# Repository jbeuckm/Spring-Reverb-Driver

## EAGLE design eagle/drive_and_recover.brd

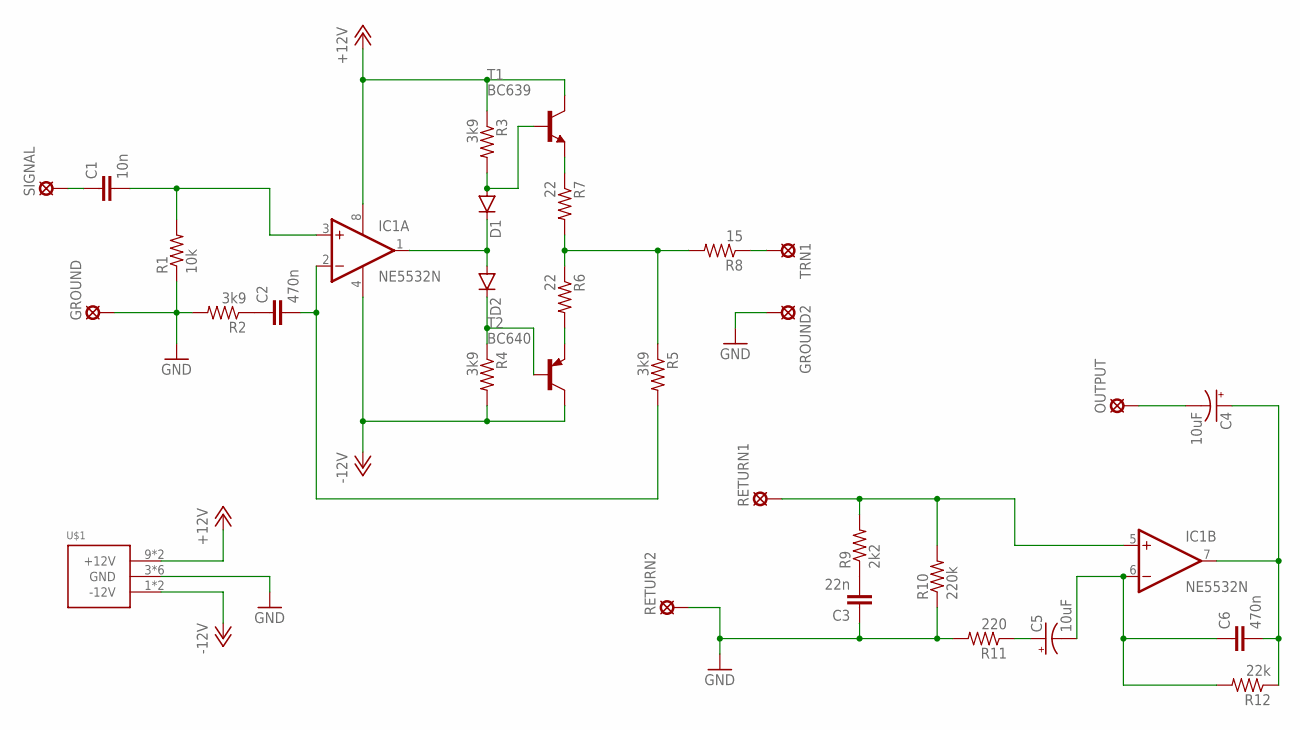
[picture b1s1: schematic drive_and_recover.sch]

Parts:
C1: 10n; CAP-PTH-SMALL
C2, C6: 470n; CAP-PTH-SMALL
C3: 22n; CAP-PTH-SMALL
C4, C5: 10uF; E2-5
D1, D2: DIODE1N4148; DIODE-1N4148
GROUND, GROUND2: LSP10
IC1: NE5532N; DIL08
OUTPUT: LSP10
R1: 10k; AXIAL-0.4
R2, R3, R4, R5: 3k9; AXIAL-0.4
R6, R7: 22; AXIAL-0.4
R8: 15; AXIAL-0.4
R9: 2k2; AXIAL-0.4
R10: 220k; AXIAL-0.4
R11: 220; AXIAL-0.4
R12: 22k; AXIAL-0.4
RETURN1, RETURN2: LSP10
SIGNAL: LSP10
T1: BC639; TO92-ECB
T2: BC640; TO92-BCE
TRN1: LSP10
U$1: POWER_SIMPLE16; POWER_16

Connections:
+12V: IC1.8 (V+), R3.P$1 (1), T1.C, U$1.9 (+12V), U$1.10 (+12V)
-12V: IC1.4 (V-), R4.P$2 (2), T2.C, U$1.1 (-12V), U$1.2 (-12V)
GND: C3.1, GROUND.MP, GROUND2.MP, R1.P$1 (1), R2.P$2 (2), R10.P$1 (1), R11.P$2 (2), RETURN2.MP, U$1.3 (GND), U$1.4 (GND), U$1.5 (GND), U$1.6 (GND), U$1.7 (GND), U$1.8 (GND)
unnamed: C1.1, SIGNAL.MP
unnamed: C1.2, IC1.3 (+IN), R1.P$2 (2)
unnamed: D1.C, D2.A, IC1.1 (OUT)
unnamed: C2.1, R2.P$1 (1)
unnamed: D1.A, R3.P$2 (2), T1.B
unnamed: C2.2, IC1.2 (-IN), R5.P$2 (2)
unnamed: C3.2, R9.P$1 (1)
unnamed: C5.+, R11.P$1 (1)
unnamed: IC1.5 (+IN), R9.P$2 (2), R10.P$2 (2), RETURN1.MP
unnamed: C4.-, OUTPUT.MP
unnamed: D2.C, R4.P$1 (1), T2.B
unnamed: R5.P$1 (1), R6.P$1 (1), R7.P$2 (2), R8.P$2 (2)
unnamed: C5.-, C6.1, IC1.6 (-IN), R12.P$2 (2)
unnamed: R7.P$1 (1), T1.E
unnamed: R6.P$2 (2), T2.E
unnamed: C4.+, C6.2, IC1.7 (OUT), R12.P$1 (1)
unnamed: R8.P$1 (1), TRN1.MP

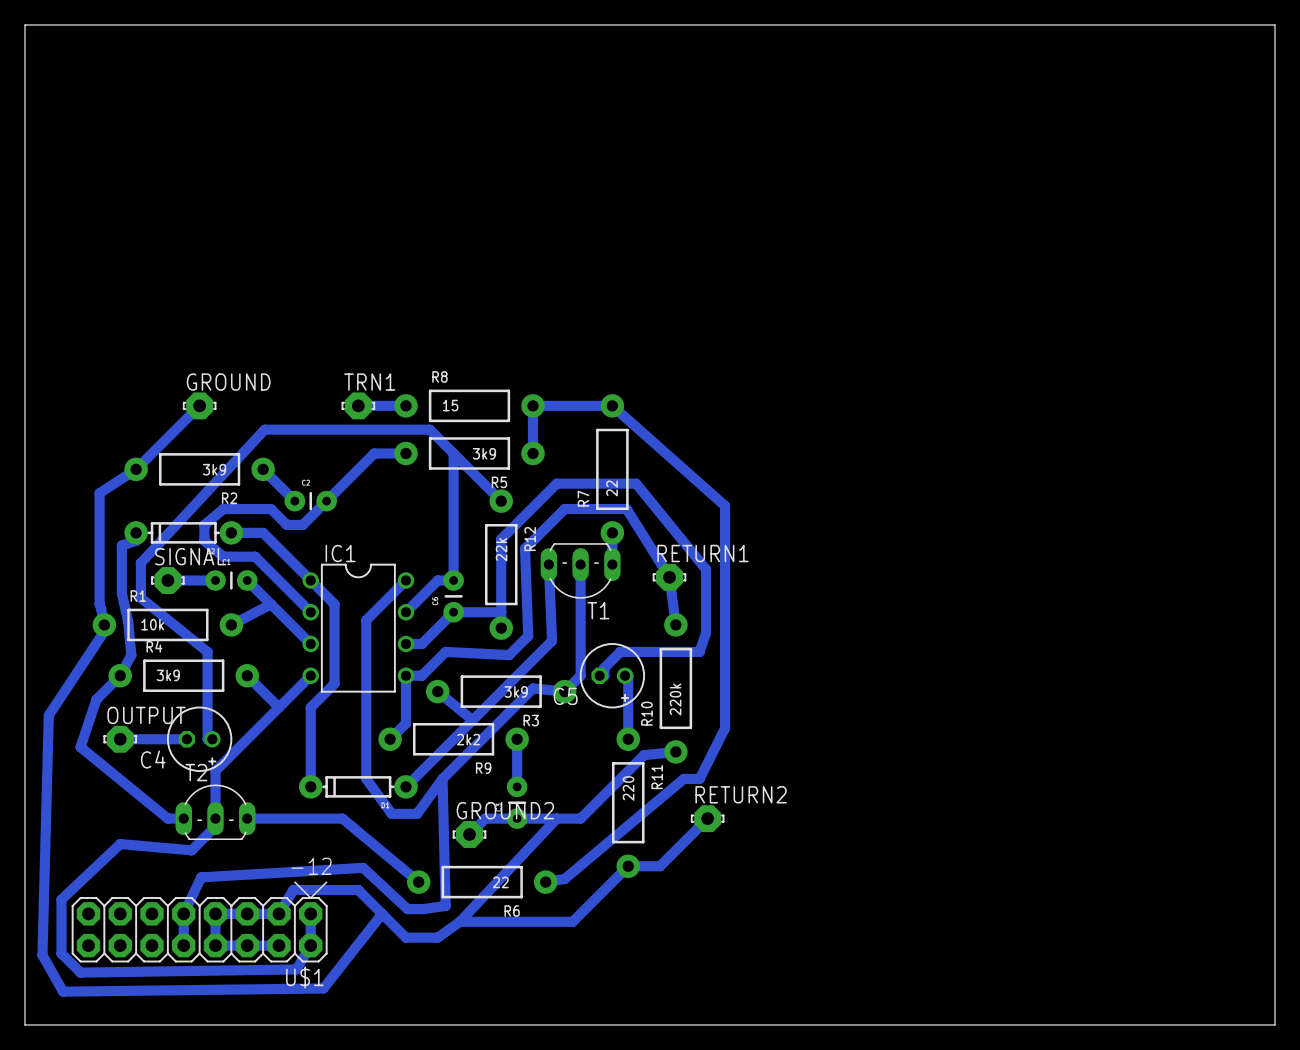
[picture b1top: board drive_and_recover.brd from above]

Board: 2 copper layers, 100.0 x 80.0 mm, 31 parts (0 on the bottom side), 20 nets.

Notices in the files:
parts and their libraries:
SparkFun-Capacitors: Licensing: Creative Commons ShareAlike 4.0 International - https://creativecommons.org/licenses/by-sa/4.0
